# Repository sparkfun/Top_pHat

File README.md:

SparkFun Top pHAT for Raspberry Pi
========================================

[*SparkFun Top pHAT for Raspberry Pi (DEV-16653)*](https://www.sparkfun.com/products/16653)

The Top pHAT for Raspberry Pi is a pHAT that includes a 2.4" TFT Display connected to SPI, a WM8960 Audio Codec connected to I2S with stereo microphones and a single speaker, 6 WS2812 LED's, along with buttons and a joystick that are attached to an ATTiny that controls button presses and lives on the I2C Bus. This board is perfect for your next machine learning project with it's audio and display capabilities.

The ATTiny is programmed with the Qwiic Button Firmware. For source code, fuse settings and more information please see that products repo here:

[https://github.com/sparkfun/Qwiic_Button](https://github.com/sparkfun/Qwiic_Button)

Repository Contents
-------------------

* **/Firmware** - Firmware for the ATTiny to control the buttons
* **/Hardware** - Eagle design files (.brd, .sch)
* **/Production** - Production panel files (.brd)

Documentation
--------------
* **[Hookup Guide](https://learn.sparkfun.com/tutorials/sparkfun-top-phat-hookup-guide)** - Basic hookup guide for the SparkFun Top pHAT.

Product Versions
--------------
* [**DEV-16653**](https://www.sparkfun.com/products/16653) - Updated release with non-touch screen (as originally designed)
* [**DEV-16301**](https://www.sparkfun.com/products/16301) - Initial release with touch screen (due to supply issue; touch pins not connected)

License Information
-------------------

This product is _**open source**_! 

Please review the LICENSE.md file for license information. 

If you have any questions or concerns on licensing, please contact technical support on our [SparkFun forums](https://forum.sparkfun.com/viewforum.php?f=152).

Distributed as-is; no warranty is given.

- Your friends at SparkFun.

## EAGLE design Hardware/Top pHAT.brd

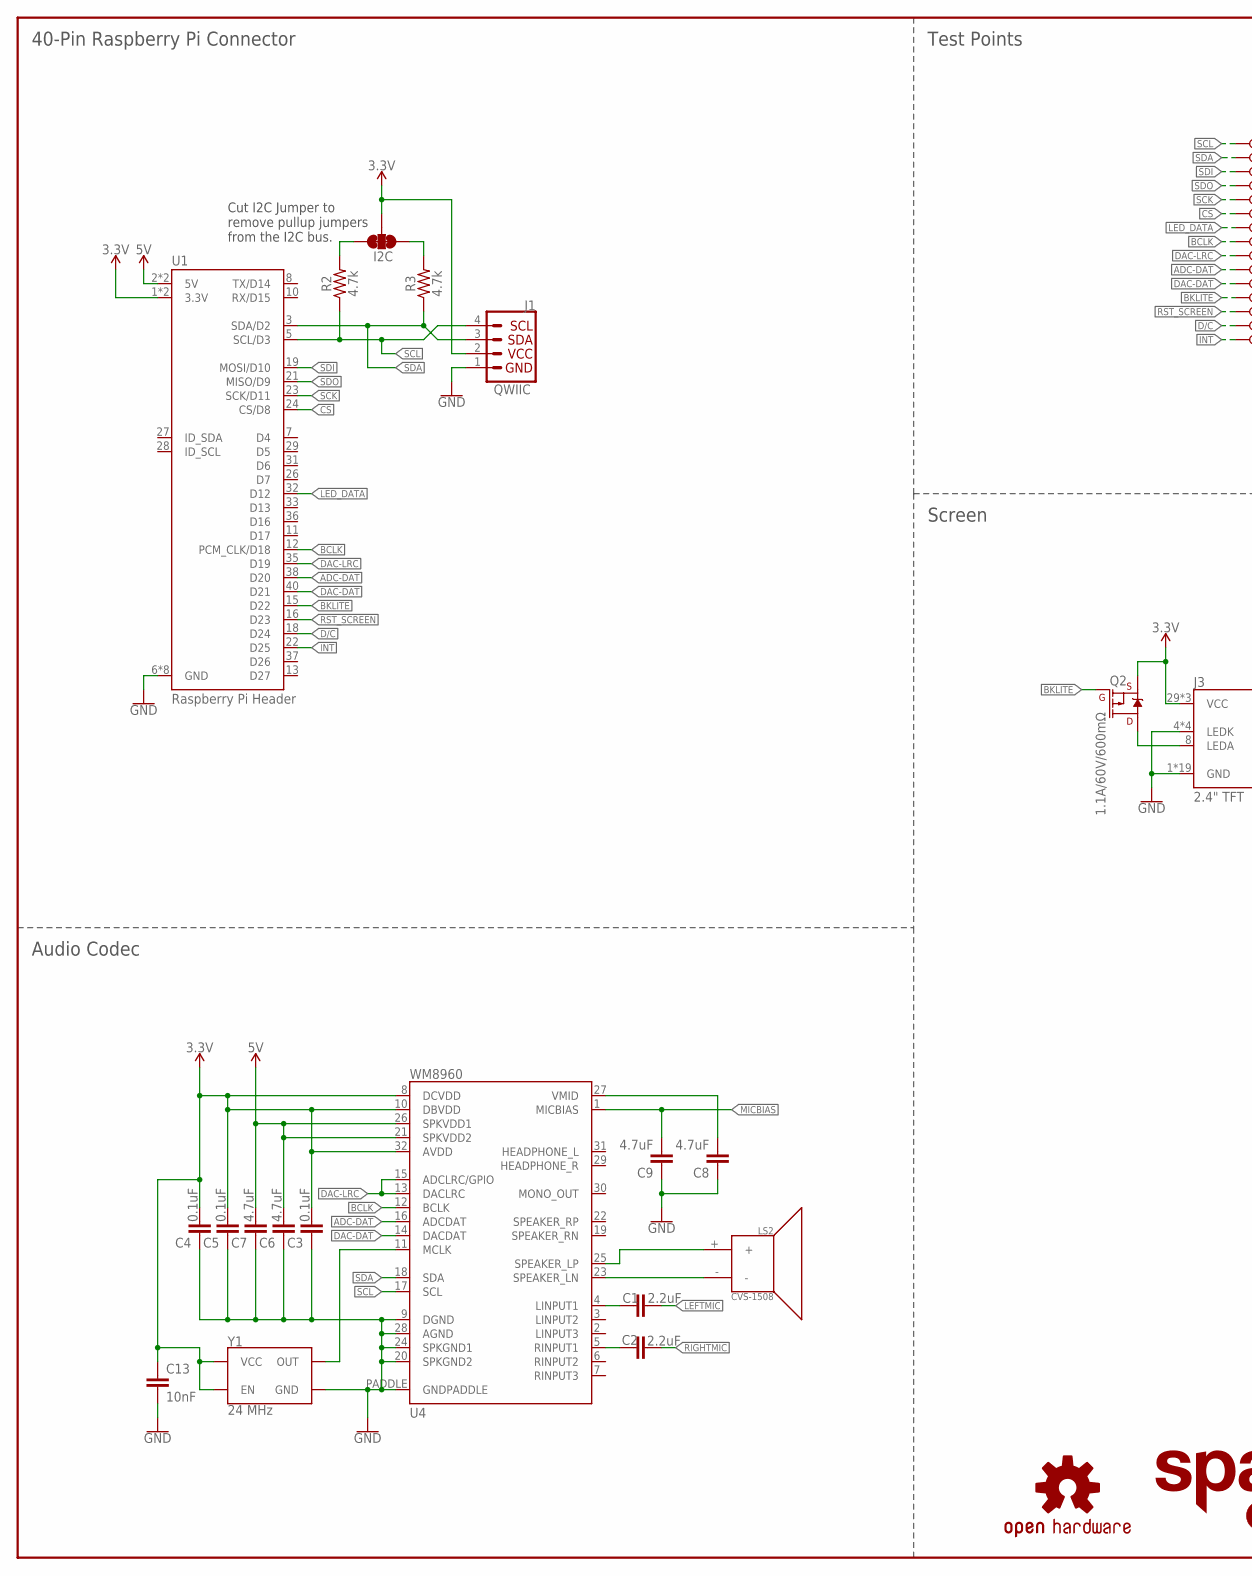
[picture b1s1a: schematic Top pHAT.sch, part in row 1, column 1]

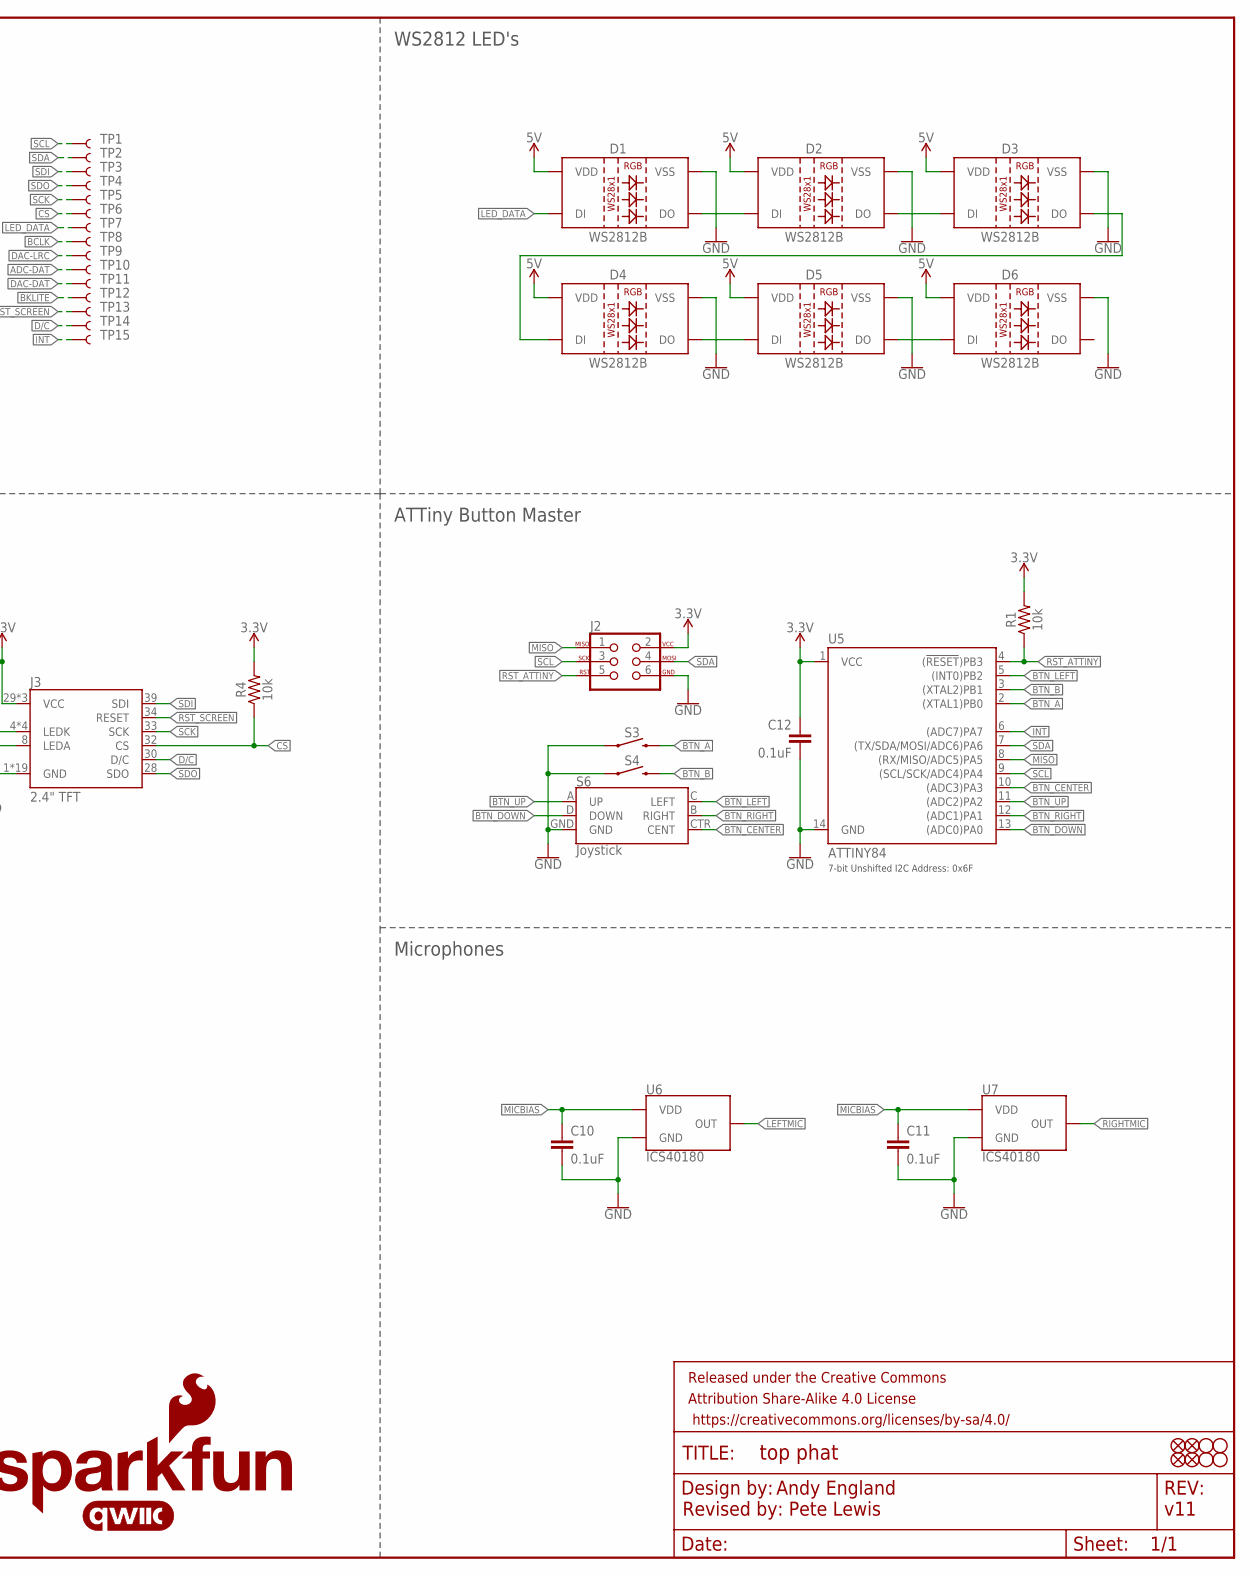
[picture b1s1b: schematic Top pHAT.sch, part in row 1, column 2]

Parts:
C1, C2: 2.2uF; 0603
C3, C4, C5, C10, C11, C12: 0.1uF; 0603
C6, C7, C8, C9: 4.7uF; 0603
C13: 10nF; 0603
D1, D2, D3, D4, D5, D6: WS2812B
FD1, FD2, FD3, FD4: FIDUCIAL1X2; FIDUCIAL-1X2
FRAME1: FRAME-LEDGER; CREATIVE_COMMONS
H1, H2, H3, H4: STAND-OFFTIGHT; STAND-OFF-TIGHT
I2C: JUMPER-SMT_3_2-NC_TRACE_NO-SILK; SMT-JUMPER_3_2-NC_TRACE_NO-SILK
J1: QWIIC; JST04_1MM_RA
J2: AVR_SPI_PROG_3X2TESTPOINTS; 2X3_TEST_POINTS
J3: 2.4" TFT; FPC05040-17204
LOGO2: SFE_LOGO_NAME_FLAME.4_INCH; SFE_LOGO_NAME_FLAME_.4
LOGO3: QWIIC_LOGO_4MM; QWIIC_4MM
LOGO4: OSHW-LOGOS; OSHW-LOGO-S
LS2: CVS-1508; CVS-1508_PCBSPKR
Q2: 1.1A/60V/600mΩ; SOT23-3
R1, R4: 10k; 0603
R2, R3: 4.7k; 0603
S3, S4: MOMENTARY-SWITCH-SPST-SMD-5.2MM-TALL; TACTILE_SWITCH_SMD_5.2MM
S6: Joystick; JOYSTICK_MINI
TP1, TP2, TP3, TP4, TP5, TP6, TP7, TP8, TP9, TP10, TP11, TP12, TP13, TP14, TP15: TEST-POINT3X5; PAD.03X.05
U1: Raspberry Pi Header; RASPBERRY_PI_SHIELD_BOTTOM_ENTRY_NOHOLES
U4: WM8960; QFN-32
U5: ATTINY84; SO14
U6, U7: ICS40180
Y1: 24 MHz; RESONATOR-SMD-3.2X2.5

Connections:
3.3V: C3.2, C4.2, C5.2, C12.1, C13.1, I2C.2, J1.2, J2.2, J3.29 (VCC), J3.31 (VCC), J3.38 (VCC), Q2.2 (S), R1.2, R4.2, U1.1 (3.3V), U1.17 (3.3V), U4.8 (DCVDD), U4.10 (DBVDD), U4.32 (AVDD), U5.1 (VCC), Y1.1 (EN), Y1.4 (VCC)
5V: C6.2, C7.2, D1.1 (VDD), D2.1 (VDD), D3.1 (VDD), D4.1 (VDD), D5.1 (VDD), D6.1 (VDD), U1.2 (5V), U1.4 (5V), U4.21 (SPKVDD2), U4.26 (SPKVDD1)
!BKLITE: Q2.1 (G), TP12.P$1, U1.15 (D22)
!CS: J3.32 (CS), R4.1, TP6.P$1, U1.24 (CS/D8)
!INT: TP15.P$1, U1.22 (D25), U5.6 ((ADC7)PA7)
!RST_ATTINY: J2.5, R1.1, U5.4 ((!RESET!)PB3)
!RST_SCREEN: J3.34 (RESET), TP13.P$1, U1.16 (D23)
ADC-DAT: TP10.P$1, U1.38 (D20), U4.16 (ADCDAT)
BCLK: TP8.P$1, U1.12 (PCM_CLK/D18), U4.12 (BCLK)
BTN_A: S3.3 (2), U5.2 ((XTAL1)PB0)
BTN_B: S4.3 (2), U5.3 ((XTAL2)PB1)
BTN_CENTER: S6.CTR (CENT), U5.10 ((ADC3)PA3)
BTN_DOWN: S6.D (DOWN), U5.13 ((ADC0)PA0)
BTN_LEFT: S6.C (LEFT), U5.5 ((INT0)PB2)
BTN_RIGHT: S6.B (RIGHT), U5.12 ((ADC1)PA1)
BTN_UP: S6.A (UP), U5.11 ((ADC2)PA2)
D/C: J3.30 (D/C), TP14.P$1, U1.18 (D24)
DAC-DAT: TP11.P$1, U1.40 (D21), U4.14 (DACDAT)
DAC-LRC: TP9.P$1, U1.35 (D19), U4.13 (DACLRC), U4.15 (ADCLRC/GPIO)
GND: C3.1, C4.1, C5.1, C6.1, C7.1, C8.1, C9.1, C10.2, C11.2, C12.2, C13.2, D1.3 (VSS), D2.3 (VSS), D3.3 (VSS), D4.3 (VSS), D5.3 (VSS), D6.3 (VSS), J1.1, J2.6, J3.1 (GND), J3.4 (LEDK), J3.5 (LEDK), J3.6 (LEDK), J3.7 (LEDK), J3.11 (GND), J3.12 (GND), J3.13 (GND), J3.14 (GND), J3.15 (GND), J3.16 (GND), J3.17 (GND), J3.18 (GND), J3.19 (GND), J3.20 (GND), J3.21 (GND), J3.22 (GND), J3.23 (GND), J3.24 (GND), J3.25 (GND), J3.26 (GND), J3.27 (GND), J3.40 (GND), S3.1, S4.1, S6.GND, U1.6 (GND), U1.9 (GND), U1.14 (GND), U1.20 (GND), U1.25 (GND), U1.30 (GND), U1.34 (GND), U1.39 (GND), U4.9 (DGND), U4.20 (SPKGND2), U4.24 (SPKGND1), U4.28 (AGND), U4.PADDLE (GNDPADDLE), U5.14 (GND), U6.2 (GND), U6.3 (GND), U6.4 (GND), U7.2 (GND), U7.3 (GND), U7.4 (GND), Y1.2 (GND)
LED_DATA: D1.4 (DI), TP7.P$1, U1.32 (D12)
LEFTMIC: C1.2, U6.1 (OUT)
MICBIAS: C9.2, C10.1, C11.1, U4.1 (MICBIAS), U6.5 (VDD), U7.5 (VDD)
MISO: J2.1, U5.8 ((RX/MISO/ADC5)PA5)
unnamed: D3.2 (DO), D4.4 (DI)
unnamed: D4.2 (DO), D5.4 (DI)
unnamed: D5.2 (DO), D6.4 (DI)
unnamed: J3.8 (LEDA), Q2.3 (D)
unnamed: LS2.+, U4.25 (SPEAKER_LP)
unnamed: D1.2 (DO), D2.4 (DI)
unnamed: D2.2 (DO), D3.4 (DI)
unnamed: U4.11 (MCLK), Y1.3 (OUT)
unnamed: I2C.3, R2.2
unnamed: I2C.1, R3.2
unnamed: LS2.-, U4.23 (SPEAKER_LN)
unnamed: C1.1, U4.4 (LINPUT1)
unnamed: C2.1, U4.5 (RINPUT1)
unnamed: C8.2, U4.27 (VMID)
RIGHTMIC: C2.2, U7.1 (OUT)
SCK: J3.33 (SCK), TP5.P$1, U1.23 (SCK/D11)
SCL: J1.4, J2.3, R2.1, TP1.P$1, U1.5 (SCL/D3), U4.17 (SCL), U5.9 ((SCL/SCK/ADC4)PA4)
SDA: J1.3, J2.4, R3.1, TP2.P$1, U1.3 (SDA/D2), U4.18 (SDA), U5.7 ((TX/SDA/MOSI/ADC6)PA6)
SDI: J3.39 (SDI), TP3.P$1, U1.19 (MOSI/D10)
SDO: J3.28 (SDO), TP4.P$1, U1.21 (MISO/D9)

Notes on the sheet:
Andy England
Screen
40-Pin Raspberry Pi Connector
Audio Codec
Microphones
ATTiny Button Master
WS2812 LED's
Cut I2C Jumper to remove pullup jumpers from the I2C bus.
7-bit Unshifted I2C Address: 0x6F
v11
Test Points
Revised by: Pete Lewis

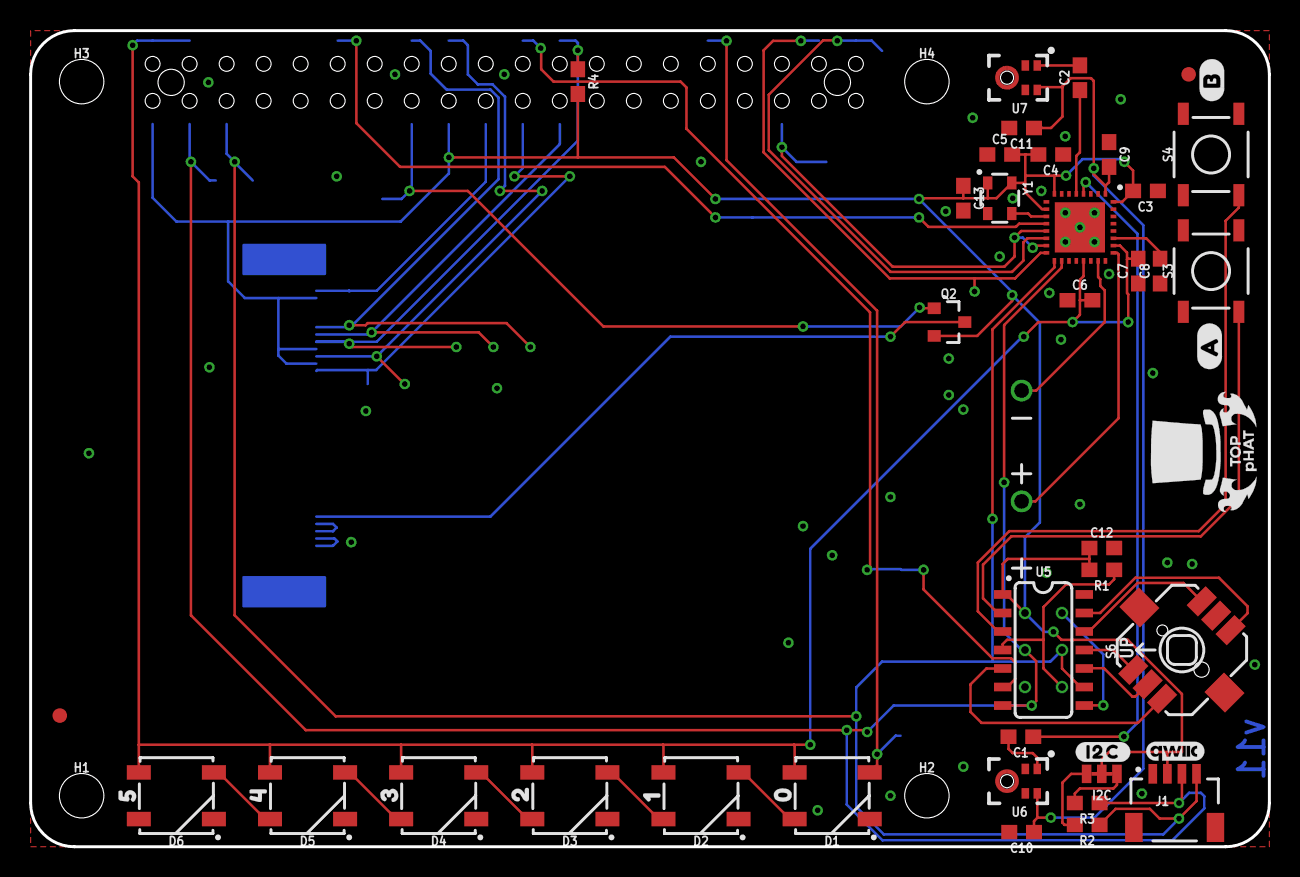
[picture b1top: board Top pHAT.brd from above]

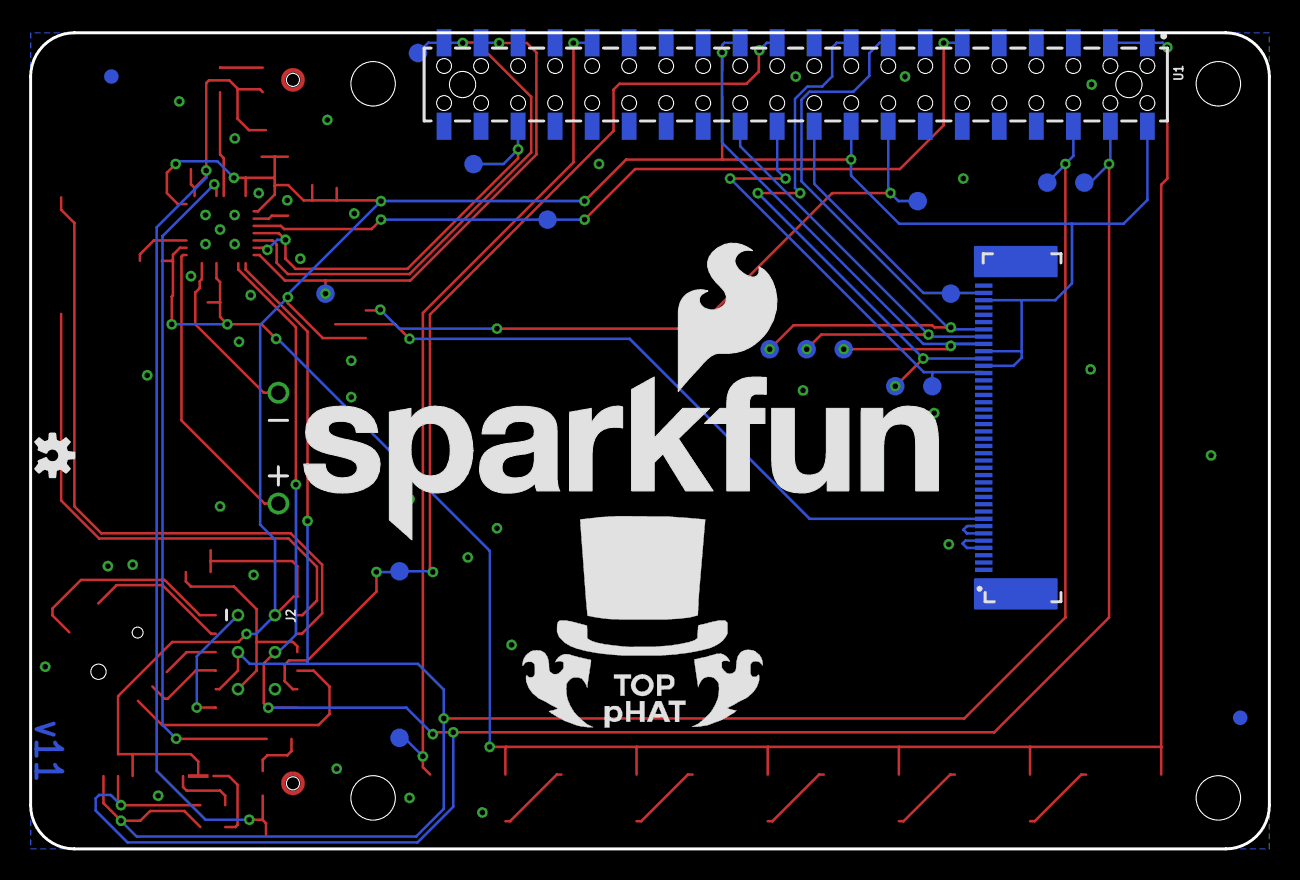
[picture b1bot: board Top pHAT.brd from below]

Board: 2 copper layers, 85.0 x 56.0 mm, 76 parts (23 on the bottom side), 44 nets.

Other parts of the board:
U$1: TOP_PHAT_LOGO_BIG
U$2: #B#0
U$4: TOP_PHAT_LOGO_SMALL
U$6: #I2C#0
U$7: #A#0
U$8: 00
U$13: 10
U$14: 20
U$15: 30
U$16: 40
U$17: 50

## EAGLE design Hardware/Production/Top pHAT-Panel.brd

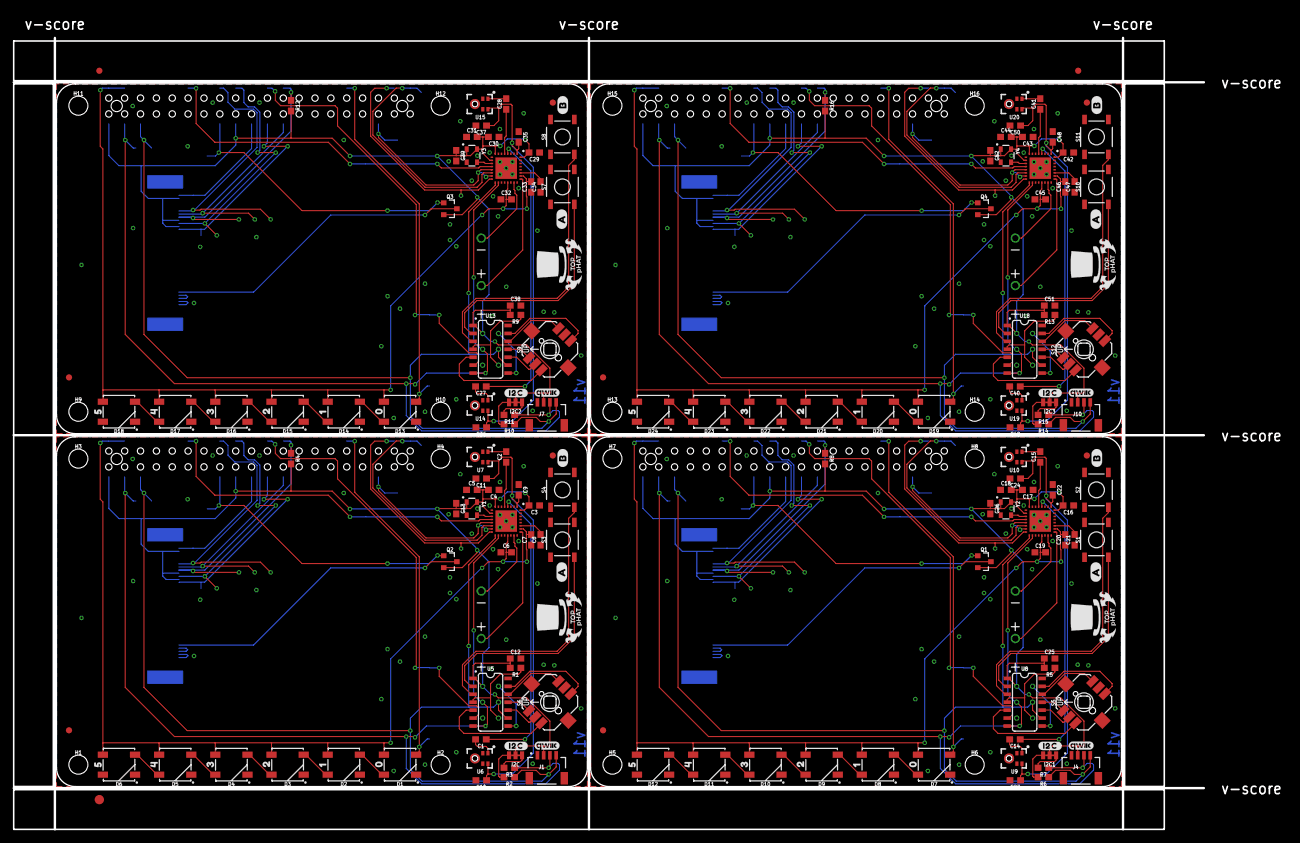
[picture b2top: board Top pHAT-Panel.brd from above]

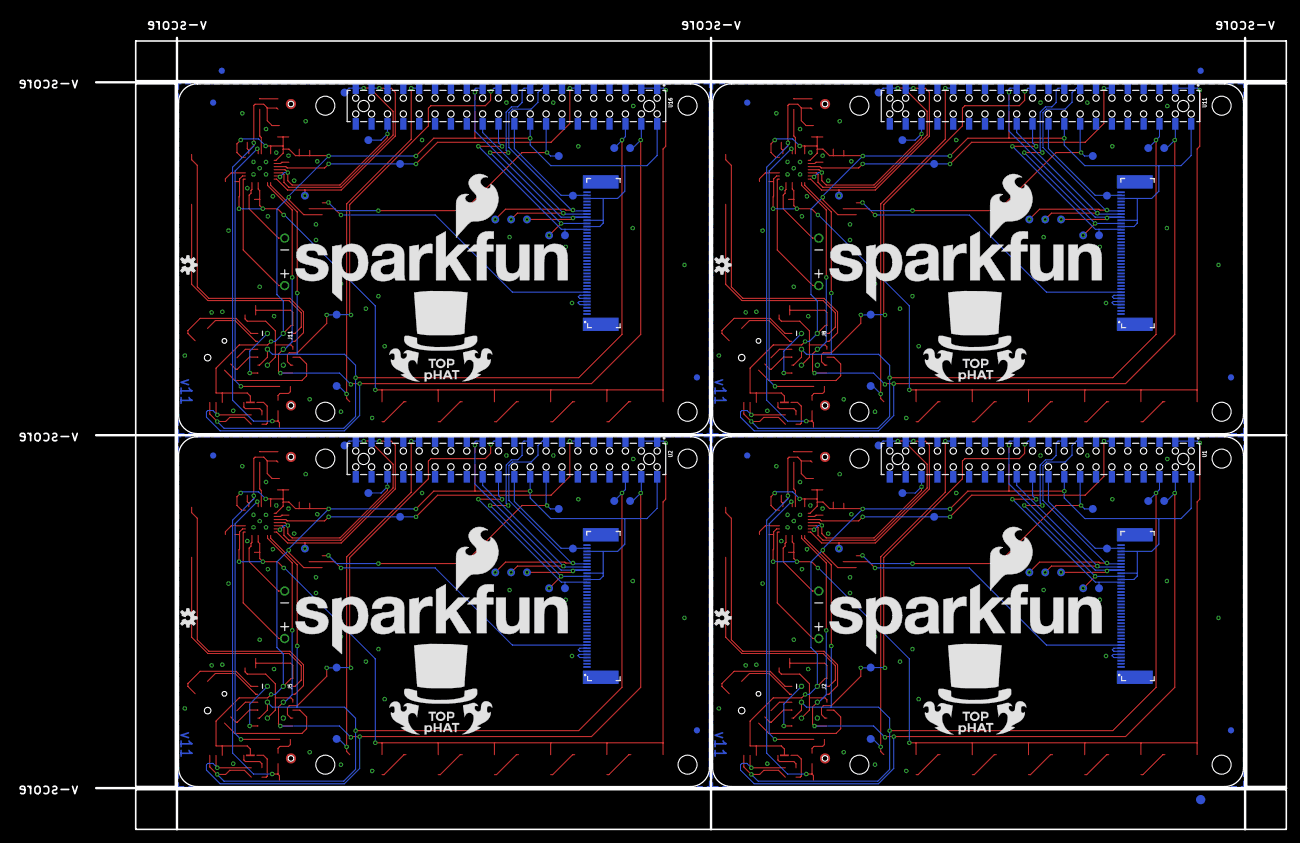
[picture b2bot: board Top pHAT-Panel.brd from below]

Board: 2 copper layers, 203.8 x 130.6 mm, 306 parts (95 on the bottom side), 176 nets.

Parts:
C1, C2, C14, C15, C27, C28, C40, C41: 2.2uF; 0603
C3, C4, C5, C10, C11, C12, C16, C17, C18, C23, C24, C25, C29, C30, C31, C36, C37, C38, C42, C43, C44, C49, C50, C51: 0.1uF; 0603
C6, C7, C8, C9, C19, C20, C21, C22, C32, C33, C34, C35, C45, C46, C47, C48: 4.7uF; 0603
C13, C26, C39, C52: 10nF; 0603
D1, D2, D3, D4, D5, D6, D7, D8, D9, D10, D11, D12, D13, D14, D15, D16, D17, D18, D19, D20, D21, D22, D23, D24: WS2812B
E$1, E$2, E$3, E$4: FIDUCIAL-1X2
E$5, E$6: FIDUCIAL-1.5X3
FD1, FD2, FD3, FD4, FD5, FD6, FD7, FD8, FD9, FD10, FD11, FD12, FD13, FD14, FD15, FD16: FIDUCIAL1X2; FIDUCIAL-1X2
H1, H2, H3, H4, H5, H6, H7, H8, H9, H10, H11, H12, H13, H14, H15, H16: STAND-OFFTIGHT; STAND-OFF-TIGHT
I2C, I2C1, I2C2, I2C3: JUMPER-SMT_3_2-NC_TRACE_NO-SILK; SMT-JUMPER_3_2-NC_TRACE_NO-SILK
J1, J4, J7, J10: QWIIC; JST04_1MM_RA
J2, J5, J8, J11: AVR_SPI_PROG_3X2TESTPOINTS; 2X3_TEST_POINTS
J3, J6, J9, J12: 2.4" TFT; FPC05040-17204
LOGO1, LOGO2, LOGO7, LOGO10: SFE_LOGO_NAME_FLAME.4_INCH; SFE_LOGO_NAME_FLAME_.4
LOGO3, LOGO5, LOGO8, LOGO11: QWIIC_LOGO_4MM; QWIIC_4MM
LOGO4, LOGO6, LOGO9, LOGO12: OSHW-LOGOS; OSHW-LOGO-S
LS1, LS2, LS3, LS4: CVS-1508; CVS-1508_PCBSPKR
Q1, Q2, Q3, Q4: 1.1A/60V/600mΩ; SOT23-3
R1, R4, R5, R8, R9, R12, R13, R16: 10k; 0603
R2, R3, R6, R7, R10, R11, R14, R15: 4.7k; 0603
S1, S2, S3, S4, S7, S8, S10, S11: MOMENTARY-SWITCH-SPST-SMD-5.2MM-TALL; TACTILE_SWITCH_SMD_5.2MM
S5, S6, S9, S12: Joystick; JOYSTICK_MINI
TP1, TP2, TP3, TP4, TP5, TP6, TP7, TP8, TP9, TP10, TP11, TP12, TP13, TP14, TP15, TP16, TP17, TP18, TP19, TP20, TP21, TP22, TP23, TP24, TP25, TP26, TP27, TP28, TP29, TP30, TP31, TP32, TP33, TP34, TP35, TP36, TP37, TP38, TP39, TP40, TP41, TP42, TP43, TP44, TP45, TP46, TP47, TP48, TP49, TP50, TP51, TP52, TP53, TP54, TP55, TP56, TP57, TP58, TP59, TP60: TEST-POINT3X5; PAD.03X.05
U1, U2, U11, U16: Raspberry Pi Header; RASPBERRY_PI_SHIELD_BOTTOM_ENTRY_NOHOLES
U3, U4, U12, U17: WM8960; QFN-32
U5, U8, U13, U18: ATTINY84; SO14
U6, U7, U9, U10, U14, U15, U19, U20: ICS40180
U$1, U$22, U$33, U$44: TOP_PHAT_LOGO_BIG
U$2, U$3, U$23, U$34: #B#0
U$4, U$21, U$32, U$43: TOP_PHAT_LOGO_SMALL
U$5, U$7, U$24, U$35: #A#0
U$6, U$9, U$25, U$36: #I2C#0
U$8, U$10, U$26, U$37: 00
U$11, U$13, U$27, U$38: 10
U$12, U$14, U$28, U$39: 20
U$15, U$18, U$29, U$40: 30
U$16, U$19, U$30, U$41: 40
U$17, U$20, U$31, U$42: 50
Y1, Y2, Y3, Y4: 24 MHz; RESONATOR-SMD-3.2X2.5

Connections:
3.3V: C3.2, C4.2, C5.2, C12.1, C13.1, I2C.2, J1.2, J2.2, J3.29, J3.31, J3.38, Q2.2, R1.2, R4.2, U1.1, U1.17, U4.8, U4.10, U4.32, U5.1, Y1.1, Y1.4
3.3V1: C16.2, C17.2, C18.2, C25.1, C26.1, I2C1.2, J4.2, J5.2, J6.29, J6.31, J6.38, Q1.2, R5.2, R8.2, U2.1, U2.17, U3.8, U3.10, U3.32, U8.1, Y2.1, Y2.4
3.3V2: C29.2, C30.2, C31.2, C38.1, C39.1, I2C2.2, J7.2, J8.2, J9.29, J9.31, J9.38, Q3.2, R9.2, R12.2, U11.1, U11.17, U12.8, U12.10, U12.32, U13.1, Y3.1, Y3.4
3.3V3: C42.2, C43.2, C44.2, C51.1, C52.1, I2C3.2, J10.2, J11.2, J12.29, J12.31, J12.38, Q4.2, R13.2, R16.2, U16.1, U16.17, U17.8, U17.10, U17.32, U18.1, Y4.1, Y4.4
5V: C6.2, C7.2, D1.1, D2.1, D3.1, D4.1, D5.1, D6.1, U1.2, U1.4, U4.21, U4.26
5V1: C19.2, C20.2, D7.1, D8.1, D9.1, D10.1, D11.1, D12.1, U2.2, U2.4, U3.21, U3.26
5V2: C32.2, C33.2, D13.1, D14.1, D15.1, D16.1, D17.1, D18.1, U11.2, U11.4, U12.21, U12.26
5V3: C45.2, C46.2, D19.1, D20.1, D21.1, D22.1, D23.1, D24.1, U16.2, U16.4, U17.21, U17.26
!BKLITE: Q2.1, TP12.P$1, U1.15
!BKLITE1: Q1.1, TP27.P$1, U2.15
!BKLITE2: Q3.1, TP42.P$1, U11.15
!BKLITE3: Q4.1, TP57.P$1, U16.15
!CS: J3.32, R4.1, TP6.P$1, U1.24
!CS1: J6.32, R8.1, TP21.P$1, U2.24
!CS2: J9.32, R12.1, TP36.P$1, U11.24
!CS3: J12.32, R16.1, TP51.P$1, U16.24
!INT: TP15.P$1, U1.22, U5.6
!INT1: TP30.P$1, U2.22, U8.6
!INT2: TP45.P$1, U11.22, U13.6
!INT3: TP60.P$1, U16.22, U18.6
!RST_ATTINY: J2.5, R1.1, U5.4
!RST_ATTINY1: J5.5, R5.1, U8.4
!RST_ATTINY2: J8.5, R9.1, U13.4
!RST_ATTINY3: J11.5, R13.1, U18.4
!RST_SCREEN: J3.34, TP13.P$1, U1.16
!RST_SCREEN1: J6.34, TP28.P$1, U2.16
!RST_SCREEN2: J9.34, TP43.P$1, U11.16
!RST_SCREEN3: J12.34, TP58.P$1, U16.16
ADC-DAT: TP10.P$1, U1.38, U4.16
ADC-DAT1: TP25.P$1, U2.38, U3.16
ADC-DAT2: TP40.P$1, U11.38, U12.16
ADC-DAT3: TP55.P$1, U16.38, U17.16
BCLK: TP8.P$1, U1.12, U4.12
BCLK1: TP23.P$1, U2.12, U3.12
BCLK2: TP38.P$1, U11.12, U12.12
BCLK3: TP53.P$1, U16.12, U17.12
BTN_A: S3.3, U5.2
BTN_A1: S1.3, U8.2
BTN_A2: S7.3, U13.2
BTN_A3: S10.3, U18.2
BTN_B: S4.3, U5.3
BTN_B1: S2.3, U8.3
BTN_B2: S8.3, U13.3
BTN_B3: S11.3, U18.3
BTN_CENTER: S6.CTR, U5.10
BTN_CENTER1: S5.CTR, U8.10
BTN_CENTER2: S9.CTR, U13.10
BTN_CENTER3: S12.CTR, U18.10
BTN_DOWN: S6.D, U5.13
BTN_DOWN1: S5.D, U8.13
BTN_DOWN2: S9.D, U13.13
BTN_DOWN3: S12.D, U18.13
BTN_LEFT: S6.C, U5.5
BTN_LEFT1: S5.C, U8.5
BTN_LEFT2: S9.C, U13.5
BTN_LEFT3: S12.C, U18.5
BTN_RIGHT: S6.B, U5.12
BTN_RIGHT1: S5.B, U8.12
BTN_RIGHT2: S9.B, U13.12
BTN_RIGHT3: S12.B, U18.12
BTN_UP: S6.A, U5.11
BTN_UP1: S5.A, U8.11
BTN_UP2: S9.A, U13.11
BTN_UP3: S12.A, U18.11
D/C: J3.30, TP14.P$1, U1.18
D/C1: J6.30, TP29.P$1, U2.18
D/C2: J9.30, TP44.P$1, U11.18
D/C3: J12.30, TP59.P$1, U16.18
DAC-DAT: TP11.P$1, U1.40, U4.14
DAC-DAT1: TP26.P$1, U2.40, U3.14
DAC-DAT2: TP41.P$1, U11.40, U12.14
DAC-DAT3: TP56.P$1, U16.40, U17.14
DAC-LRC: TP9.P$1, U1.35, U4.13, U4.15
DAC-LRC1: TP24.P$1, U2.35, U3.13, U3.15
DAC-LRC2: TP39.P$1, U11.35, U12.13, U12.15
DAC-LRC3: TP54.P$1, U16.35, U17.13, U17.15
GND: C3.1, C4.1, C5.1, C6.1, C7.1, C8.1, C9.1, C10.2, C11.2, C12.2, C13.2, D1.3, D2.3, D3.3, D4.3, D5.3, D6.3, J1.1, J2.6, J3.1, J3.4, J3.5, J3.6, J3.7, J3.11, J3.12, J3.13, J3.14, J3.15, J3.16, J3.17, J3.18, J3.19, J3.20, J3.21, J3.22, J3.23, J3.24, J3.25, J3.26, J3.27, J3.40, S3.1, S4.1, S6.GND, U1.6, U1.9, U1.14, U1.20, U1.25, U1.30, U1.34, U1.39, U4.9, U4.20, U4.24, U4.28, U4.PADDLE, U5.14, U6.2, U6.3, U6.4, U7.2, U7.3, U7.4, Y1.2
GND1: C16.1, C17.1, C18.1, C19.1, C20.1, C21.1, C22.1, C23.2, C24.2, C25.2, C26.2, D7.3, D8.3, D9.3, D10.3, D11.3, D12.3, J4.1, J5.6, J6.1, J6.4, J6.5, J6.6, J6.7, J6.11, J6.12, J6.13, J6.14, J6.15, J6.16, J6.17, J6.18, J6.19, J6.20, J6.21, J6.22, J6.23, J6.24, J6.25, J6.26, J6.27, J6.40, S1.1, S2.1, S5.GND, U2.6, U2.9, U2.14, U2.20, U2.25, U2.30, U2.34, U2.39, U3.9, U3.20, U3.24, U3.28, U3.PADDLE, U8.14, U9.2, U9.3, U9.4, U10.2, U10.3, U10.4, Y2.2
GND2: C29.1, C30.1, C31.1, C32.1, C33.1, C34.1, C35.1, C36.2, C37.2, C38.2, C39.2, D13.3, D14.3, D15.3, D16.3, D17.3, D18.3, J7.1, J8.6, J9.1, J9.4, J9.5, J9.6, J9.7, J9.11, J9.12, J9.13, J9.14, J9.15, J9.16, J9.17, J9.18, J9.19, J9.20, J9.21, J9.22, J9.23, J9.24, J9.25, J9.26, J9.27, J9.40, S7.1, S8.1, S9.GND, U11.6, U11.9, U11.14, U11.20, U11.25, U11.30, U11.34, U11.39, U12.9, U12.20, U12.24, U12.28, U12.PADDLE, U13.14, U14.2, U14.3, U14.4, U15.2, U15.3, U15.4, Y3.2
GND3: C42.1, C43.1, C44.1, C45.1, C46.1, C47.1, C48.1, C49.2, C50.2, C51.2, C52.2, D19.3, D20.3, D21.3, D22.3, D23.3, D24.3, J10.1, J11.6, J12.1, J12.4, J12.5, J12.6, J12.7, J12.11, J12.12, J12.13, J12.14, J12.15, J12.16, J12.17, J12.18, J12.19, J12.20, J12.21, J12.22, J12.23, J12.24, J12.25, J12.26, J12.27, J12.40, S10.1, S11.1, S12.GND, U16.6, U16.9, U16.14, U16.20, U16.25, U16.30, U16.34, U16.39, U17.9, U17.20, U17.24, U17.28, U17.PADDLE, U18.14, U19.2, U19.3, U19.4, U20.2, U20.3, U20.4, Y4.2
LED_DATA: D1.4, TP7.P$1, U1.32
LED_DATA1: D7.4, TP22.P$1, U2.32
LED_DATA2: D13.4, TP37.P$1, U11.32
LED_DATA3: D19.4, TP52.P$1, U16.32
LEFTMIC: C1.2, U6.1
LEFTMIC1: C14.2, U9.1
LEFTMIC2: C27.2, U14.1
LEFTMIC3: C40.2, U19.1
MICBIAS: C9.2, C10.1, C11.1, U4.1, U6.5, U7.5
MICBIAS1: C22.2, C23.1, C24.1, U3.1, U9.5, U10.5
MICBIAS2: C35.2, C36.1, C37.1, U12.1, U14.5, U15.5
MICBIAS3: C48.2, C49.1, C50.1, U17.1, U19.5, U20.5
MISO: J2.1, U5.8
MISO1: J5.1, U8.8
MISO2: J8.1, U13.8
MISO3: J11.1, U18.8
unnamed: D3.2, D4.4
unnamed: D4.2, D5.4
unnamed: D5.2, D6.4
unnamed: J3.8, Q2.3
unnamed: LS1.-, U3.23
unnamed: LS2.+, U4.25
unnamed: LS1.+, U3.25
unnamed: D1.2, D2.4
unnamed: D2.2, D3.4
unnamed: C14.1, U3.4
unnamed: U4.11, Y1.3
unnamed: C15.1, U3.5
unnamed: C21.2, U3.27
unnamed: I2C1.3, R6.2
unnamed: I2C1.1, R7.2
unnamed: I2C.3, R2.2
unnamed: I2C.1, R3.2
unnamed: D7.2, D8.4
unnamed: D8.2, D9.4
unnamed: D9.2, D10.4
unnamed: D10.2, D11.4
unnamed: LS2.-, U4.23
unnamed: D11.2, D12.4
unnamed: J6.8, Q1.3
unnamed: U3.11, Y2.3
unnamed: LS3.-, U12.23
unnamed: LS3.+, U12.25
unnamed: C27.1, U12.4
unnamed: C1.1, U4.4
unnamed: C2.1, U4.5
unnamed: C28.1, U12.5
unnamed: C34.2, U12.27
unnamed: I2C2.3, R10.2
unnamed: I2C2.1, R11.2
unnamed: D13.2, D14.4
unnamed: D14.2, D15.4
unnamed: D15.2, D16.4
unnamed: C8.2, U4.27
unnamed: D16.2, D17.4
unnamed: D17.2, D18.4
unnamed: J9.8, Q3.3
unnamed: U12.11, Y3.3
unnamed: LS4.-, U17.23
unnamed: LS4.+, U17.25
unnamed: C40.1, U17.4
unnamed: C41.1, U17.5
unnamed: C47.2, U17.27
unnamed: I2C3.3, R14.2
unnamed: I2C3.1, R15.2
unnamed: D19.2, D20.4
unnamed: D20.2, D21.4
unnamed: D21.2, D22.4
unnamed: D22.2, D23.4
unnamed: D23.2, D24.4
unnamed: J12.8, Q4.3
unnamed: U17.11, Y4.3
RIGHTMIC: C2.2, U7.1
RIGHTMIC1: C15.2, U10.1
RIGHTMIC2: C28.2, U15.1
RIGHTMIC3: C41.2, U20.1
SCK: J3.33, TP5.P$1, U1.23
SCK1: J6.33, TP20.P$1, U2.23
SCK2: J9.33, TP35.P$1, U11.23
SCK3: J12.33, TP50.P$1, U16.23
SCL: J1.4, J2.3, R2.1, TP1.P$1, U1.5, U4.17, U5.9
SCL1: J4.4, J5.3, R6.1, TP16.P$1, U2.5, U3.17, U8.9
SCL2: J7.4, J8.3, R10.1, TP31.P$1, U11.5, U12.17, U13.9
SCL3: J10.4, J11.3, R14.1, TP46.P$1, U16.5, U17.17, U18.9
SDA: J1.3, J2.4, R3.1, TP2.P$1, U1.3, U4.18, U5.7
SDA1: J4.3, J5.4, R7.1, TP17.P$1, U2.3, U3.18, U8.7
SDA2: J7.3, J8.4, R11.1, TP32.P$1, U11.3, U12.18, U13.7
SDA3: J10.3, J11.4, R15.1, TP47.P$1, U16.3, U17.18, U18.7
SDI: J3.39, TP3.P$1, U1.19
SDI1: J6.39, TP18.P$1, U2.19
SDI2: J9.39, TP33.P$1, U11.19
SDI3: J12.39, TP48.P$1, U16.19
SDO: J3.28, TP4.P$1, U1.21
SDO1: J6.28, TP19.P$1, U2.21
SDO2: J9.28, TP34.P$1, U11.21
SDO3: J12.28, TP49.P$1, U16.21

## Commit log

2020-01-16 initial schematic layout, needs screen
2020-01-31 adding in screen, ready for first design review
2020-02-03 updating int pin
2020-02-03 updating footprints, running checklist
2020-02-03 post review changes
2020-02-04 ordering prototypes, adding proto gerbers
2020-02-05 updating PROD_ID on WM8960 and LCD FPC Connector, FPC Conn doesn't show up in BOM ULP
2020-02-25 pre design review for REDs
2020-02-26 post design review
2020-02-26 Adding LED numbers
2020-02-26 updating LCD prod_id
2020-02-26 post checklist changes
2020-02-27 adding top pHAT silk
2020-02-27 removing raspi mockup files
2020-04-16 adding firmware, readme, cleaning for launch
2020-04-16 adding panel
2020-10-05 Update README.md
    Picture link broken
    Update product links
2021-03-09 v11 - mic and vector buzzards/graphics
    -swapped out the mic for the ICS-40180
    -updated labels to new vector buzzards
    -converted top phat logo into vector version, currently in mini library.
2021-03-11 first run of checklist stuff
    -CS net in schematic needed a nudge.
    -enlarged top phat logo polygon lines to 0.0005"
    -Added link to Qwiic Button repo in readme - for firmware and fusebits, if needed by user.
    -added mic datasheet for good measure.
2021-03-12 Double check - trace tweaks
    Adjusted the trace off the CS pad to avoid acute angle.
    Adjusted the 5V trace off one of the LEDs to avoid acute angle.
2021-03-16 production gerbers v11

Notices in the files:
parts and their libraries:
SparkFun-Connectors: Licensing: Creative Commons ShareAlike 4.0 International - https://creativecommons.org/licenses/by-sa/4.0
SparkFun-Aesthetics: Released under the Creative Commons Attribution Share-Alike 4.0 License
SparkFun-Aesthetics: https://creativecommons.org/licenses/by-sa/4.0
